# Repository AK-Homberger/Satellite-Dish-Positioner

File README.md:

# Satellite Dish Positioner

This is an automatical satellite dish positioner with an ESP8266 D1 Mini, a compass and an MPU. It controls the satellite dish direction with a Diseqc rotor (azimut) and a linear actuator (elevation). It uses an gyroscope device for elevation and a compass device for azimut control.

The purpose of this device is to support me on the boat with the positioning of the satellite dish from the cabin. But it is also usable for campers and mobile homes.

## Hardware
The rotor is a standard Diseqc dish motor for less than 50 Euro. But for this project we use the motor upside down to move the dish in horizontal ballance. We have to remove the cranked dish connection tube from the motor. But keep the bolt and the nut. We need them to connect the upper and lower 3D-printed joint parts. 

The ESP8266 (in D1 Mini) controls the Diseqc motor with 22 kHz tone signals as defined in the [Diseqc specification](https://www.eutelsat.com/files/PDF/DiSEqC-documentation.zip) (see bus_spec.pdf, section 5 and also positioner_appli_notice.pdf). The ESP8266 generates the signal which has to be modulated on the coax signal line of the motor. I found the necessary circuit and signal generator code on GitHub:(https://github.com/acrerd/Arduino-Diseqc-solar-tracker). Many thanks for the helpful support. That saved me a lot of time. For simplification, I only used the right part of the [circuit](https://github.com/AK-Homberger/Satellite-Dish-Positioner/blob/main/diseqc-interface.pdf) starting with the 100 Ohm resistor. The risistor is directly connected to port D5 on the D1 Mini. This is sufficient to generate a signal that the Diseqc motor is recognising.

The delay values in the Arduino code ( functions write0() and write1() ) had to be adjusted for the faster ESP8266. The delay with 21 microseconds works perfectly to generate a 22 kHz signal.

The motor gets the 12 Volt power via the coax connection. Be careful with the coax connector when the device is powerd. A shortcut between core and shield would instantly destroy the inductor coil (it can only handle about 300 mA).

The motor is able to move from -75 to +75 degrees with an accuracy of 1/16 degree. That is more than sufficient for positioning the azimut.
You just have to position the sat finder in a general south facing direction. Thats all.

The elevation is controlled with a standard small linear actuator which is available for less than 30 Euro. I use here an actuator with 50 mm length. But 25 mm should work also.

In addition to the 22 kHz logic, only four other items are required:

- Step-down-converter 12V to 5V: D24V10F5
- Compass: GY-271 from AzDelivery (install [QMC5883LCompass](https://github.com/mprograms/QMC5883LCompass) library in Arduino)
- 6 axis gyroscope: GY-521 from AzDelivery (install [TinyMPU6050](https://github.com/gabriel-milan/TinyMPU6050) library in Arduino):
- Motor driver:  Adafruit DRV8871 DC Motor Driver

**Be careful with the GY-271 from other sources. Some devices are using a HMC5883L compass instead of a QMC5883L. We need the QMC5883L for this project.**

The compass and the gyroscope are connected to the I2C bus of the D1 Mini (using D1=SCL and D2=SDA). The compass is inside the box on the pcb. The gyroscope is connected with a short 4-wire cable and placed on the back of the satellite dish.

The motor driver is using ports D0 and D6. The 22 kHz signal is generated on port D5.

Schematics and PCB layout is in KiCAD folder.

## Software
The positioner is controlled with a web interface. The ssid and password for WLAN has to be set in the code.

The device is pre-configured for Astra 19.2 and my home location. Please change this for your location and satellite.
You can use one of the free calculators to get the angles for your location and desired setellite (e.g. https://www.satlex.us/en/azel_calc.html). Use "Azimut angle" and "Elevation angle". 

The true north azimut angle needs to be corrected (Az_Offset) to match the magnetic north of the compass (sailors should know how to calculate) and to correct a possible placing error on the pcb. 

The elevation angle must be corrected (El_Offset) with a dish specific value. For my dish this is -18 degrees between dish beam angle and angle of gyroscope mount. The offset has to be calculated only once and defined in the program.

```cpp
//Enter your SSID and PASSWORD
const char* ssid = "ssid";
const char* password = "passwod";

float Astra_Az = 164, Astra_El = 30.19, El_Offset=-18, Az_Offset=-10.0;   // Astra 19.2 position and dish specific offsets
```

With the web interface you can control the positioner. You can do fine tuning for azimut/elevation and switch automatic control between Off, On and R-Off.

R-Off means automatic control for azimut is switched off. Elevation remains on. This is a kind of "night" mode because the Diseqc motor is a bit noisy when constantly re-positioning. The "-Step/Step+" buttons are changing the rotor for 1/8 degree. Which should be sufficient for the desired purpose. It is possible to change it also to 1/16 degree.

Values for Azimut, Elevation, Offsets and Motor Speed can be changed with a "Settings" web page. Changed values are stored in flash memory (EEPROM) of ESP8266. With "Motor Speed" you can define the speed of the linear actuator. The value should be about 700 and defines the Pulse Width Modulation for the actuator. If the dish begins to "swing" you can adjust the value to avoid this.

.

To improve the precision of the compass, it is necessary to calibrate the device before using it. To do the calibration, load and run the [calibration sketch](https://github.com/mprograms/QMC5883LCompass/blob/master/examples/calibration/calibration.ino) from the QMC5883L compass library.

During the calibration process the device have to be moved in all possible directions (see library example). It is probably a good idea to do the calibration before placing the pcb on the dish.

The shown six values have to be set in this line:
```
compass.setCalibration(-1598, 1511, -2365, 872, -1417, 1440);   // Do a calibration for the compass and put your values here!!!
```

For the MPU there is also an calibration function available. See library for [details](https://github.com/gabriel-milan/TinyMPU6050/blob/master/examples/ArduinoIDE_Angles_Example/ArduinoIDE_Angles_Example.ino). But due to the fact that the elevation offset has to be set anyway, it is not necessary to do the calibration for the device, to get the individual offsets.

The following line in the code:
```
experimental::ESP8266WiFiGratuitous::stationKeepAliveSetIntervalMs(5000);
```
is part of the internal [ESP8266WiFi](https://github.com/esp8266/Arduino/blob/master/libraries/ESP8266WiFi/src/ESP8266WiFiGratuitous.h) library. It solves a WLAN connection problem for my router by sending ARP packets every 5 seconds to keep the WLAN connection stable.

If you don't need this, simply comment out the line.

## 3D Prints
The connection between the sat dish and the rotor as well as the other parts are designed with OpenSCAD. The files are stored in the SCAD folder.

You can either use the .scad files with OpenSCAD or you can directly print the .stl files stored [here](https://github.com/AK-Homberger/Satellite-Dish-Positioner/tree/main/SCAD/STL).

The GY-521 gyroscope is placed on the back of the dish in a hoizonal position. The compass is on the pcb facing to south direction. For other directions do a correction in the code with "#define Az_PCB_Correction 90". I had to add 90 degrees to get south direction, 180°.

The connection between the dish and the Diseqc motor has to be very stable. I used 0.2 mm accuracy and 70% fillrate for PLA. Use of ABS is also an option.

## Parts
- Sat dish: [Link](https://www.voelkner.de/products/21807/Telestar-5103309-Camping-SAT-Anlage-ohne-Receiver-Teilnehmer-Anzahl-1.html?ref=43&offer=74abe2d23c3a61dabbbaf20649c0274a&gclid=EAIaIQobChMIhfuapsL67QIVaFXVCh3rzAHpEAYYASABEgIO9vD_BwE)
- Diseqc motor: [Link](https://www.ebay.de/itm/332284938131?chn=ps&norover=1&mkevt=1&mkrid=707-134425-41852-0&mkcid=2&itemid=332284938131&targetid=940585975411&device=c&mktype=pla&googleloc=9043858&poi=&campaignid=10203814992&mkgroupid=101937413437&rlsatarget=pla-940585975411&abcId=1145992&merchantid=112028706&gclid=EAIaIQobChMIg57du6jQ7AIVRtiyCh0ixQoGEAQYAyABEgJfgvD_BwE) or [Link](https://www.wiltanet.de/sat-empfang/diseqc-schalter-motor/diseqc-motor/diseqc-motor/a-120017)
- Linear Actuator (25 or 50 mm): [Link](https://www.ebay.de/itm/750N-25-150-mm-Linear-Actuator-elektrische-Mikro-Linearantrieb-12V-Kraft-IP65/402438285052?_trkparms=aid%3D555021%26algo%3DPL.SIMRVI%26ao%3D1%26asc%3D225078%26meid%3De5d8f347c09a4ba989a35d0217f8cb5c%26pid%3D100008%26rk%3D1%26rkt%3D11%26mehot%3Dpf%26sd%3D383778548269%26itm%3D402438285052%26pmt%3D1%26noa%3D0%26pg%3D2047675%26algv%3DSimplRVIAMLv5WebWithPLRVIOnTopCombiner&_trksid=p2047675.c100008.m2219)
- D1 Mini: AzDelivery (e.g. on Amazon) [Link](https://www.amazon.de/stores/AZDelivery/AZDelivery/page/2DB821D9-4A4B-4FD2-A50B-AE111B57FC93)
- GY-271 compass: AzDelivery (e.g. on Amazon) [Link](https://www.amazon.de/stores/AZDelivery/AZDelivery/page/2DB821D9-4A4B-4FD2-A50B-AE111B57FC93) or [Link](https://www.makershop.de/sensoren/gy-271-hmc5883l/)
- GY-521 gyroscope: AzDelivery (e.g. on Amazon) [Link](https://www.amazon.de/stores/AZDelivery/AZDelivery/page/2DB821D9-4A4B-4FD2-A50B-AE111B57FC93)
- D24V10F5 [Link](https://eckstein-shop.de/Pololu-5V-1A-Step-Down-Spannungsregler-D24V10F5)
- Adafruit DRV8871: [Link](https://eckstein-shop.de/Adafruit-DRV8871-DC-Motor-Driver-Breakout-Board-36A-Max)
- Resistor 51 Ohm [Link](https://www.reichelt.de/de/en/carbon-film-resistor-1-4-w-5-51-ohm-1-4w-51-p1441.html?&nbc=1)
- Resistor 100 Ohm [Link](https://www.reichelt.de/de/en/carbon-film-resistor-1-4-w-5-100-ohms-1-4w-100-p1336.html?&nbc=1)
- Inductor 1 mH - BOU RLB0914-102K [Link](https://www.reichelt.de/index.html?ACTION=446&LA=0&nbc=1&q=bou%20rlb0914-102k)
- Capacitor 56 nF - RND 150MKT563K2E [Link](https://www.reichelt.de/index.html?ACTION=446&LA=0&nbc=1&q=150mkt563k2e%20) or alternative MKP-X2 56N2 [Link](https://www.reichelt.de/de/en/radio-interference-suppression-capacitors-56nf-305v-rm15-mkp-x2-56n2-p173414.html?&nbc=1)
- Capacitor 3,3 µF - TON 3,3/63 [Link](https://www.reichelt.de/index.html?ACTION=446&LA=446&nbc=1&q=ton%203%2C3%2F63)
- Connector 2-pin (*2) [Link](https://www.reichelt.de/de/en/2-pin-terminal-strip-spacing-5-08-akl-101-02-p36605.html?&nbc=1)
- Connector 4-pin [Link](https://www.reichelt.de/de/en/4-pin-terminal-strip-spacing-5-08-akl-101-04-p36607.html?&nbc=1)
- DC Jack [Link](https://www.reichelt.de/de/en/connector-dc-female-bulkhead-delock-89911-p259483.html?&nbc=1)

## Updates
- Version 1.1 - 19.05.2021: Improved 22 kHz signal generation (Issue #5).
- Version 1.0 - 09.02.2021: Added pcb mount correction value. Release version 1.0
- Version 0.6 - 05.02.2021: Added settings page and storage of settings in flash memory.
- Version 0.5 - 07.11.2020: Corrected error in azimut calculation (boundary check 0-360).
- Version 0.4 - 06.11.2020: Changed PCB layout to version 1.1. Larger terminal strips (5.08 mm).
- Version 0.4 - 28.10.2020: Added permanent azimut offset.
- Version 0.3 - 26.10.2020: Separated elevation and elevation offset to work with true elevation angles from calculators. 
- Version 0.2 - 26.10.2020: Initial version.

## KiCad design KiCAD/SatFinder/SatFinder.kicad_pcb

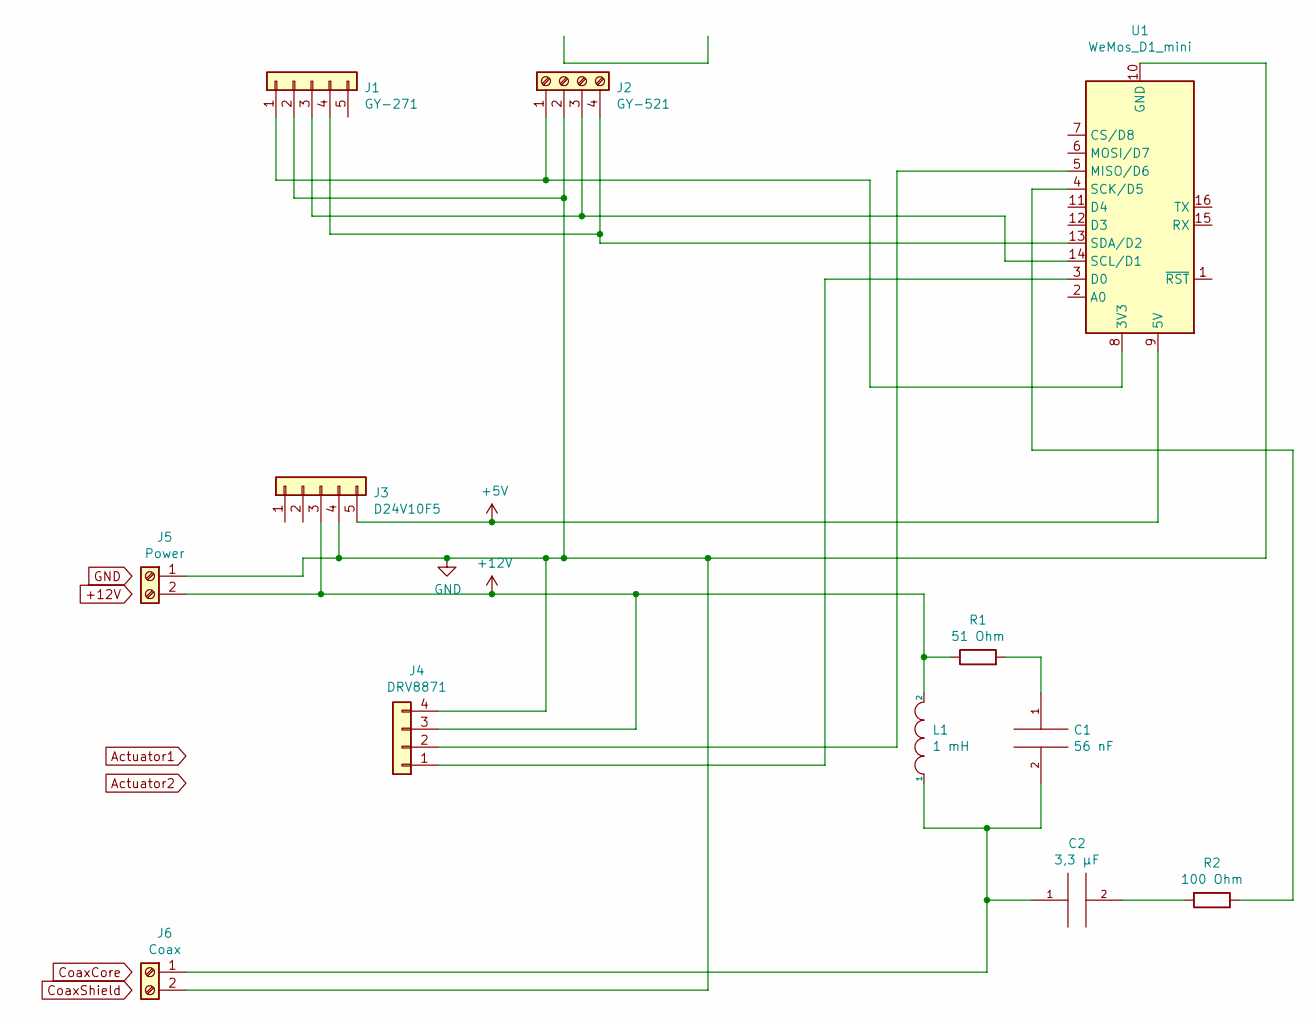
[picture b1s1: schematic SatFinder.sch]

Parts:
C1: 56 nF; C_Rect_L18.0mm_W5.0mm_P15.00mm_FKS3_FKP3
C2: 3,3 µF; CP_Axial_L18.0mm_D8.0mm_P25.00mm_Horizontal
J1: GY-271; PinHeader_1x05_P2.54mm_Vertical
J2: GY-521; TerminalBlock_bornier-4_P5.08mm
J3: D24V10F5; PinHeader_1x05_P2.54mm_Vertical
J4: DRV8871; PinHeader_1x04_P2.54mm_Vertical
J5: Power; TerminalBlock_bornier-2_P5.08mm
J6: Coax; TerminalBlock_bornier-2_P5.08mm
L1: 1 mH; L_Radial_D8.7mm_P5.00mm_Fastron_07HCP
R1: 51 Ohm; R_Axial_DIN0207_L6.3mm_D2.5mm_P7.62mm_Horizontal
R2: 100 Ohm; R_Axial_DIN0207_L6.3mm_D2.5mm_P7.62mm_Horizontal
U1: WeMos_D1_mini; WEMOS_D1_mini_light

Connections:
+5V: J3.5, U1.9 (5V)
+12V: J3.3, J4.3, J5.2, L1.2, R1.1
GND: J1.2, J2.2, J3.4, J4.4, J5.1, J6.2, U1.10 (GND)
unnamed: C1.1, R1.2
unnamed: C1.2, C2.1, J6.1, L1.1
unnamed: C2.2, R2.2
unnamed: J1.1, J2.1, U1.8 (3V3)
unnamed: J1.3, J2.3, U1.14 (SCL/D1)
unnamed: J1.4, J2.4, U1.13 (SDA/D2)
unnamed: J4.1, U1.3 (D0)
unnamed: J4.2, U1.5 (MISO/D6)
unnamed: R2.1, U1.4 (SCK/D5)

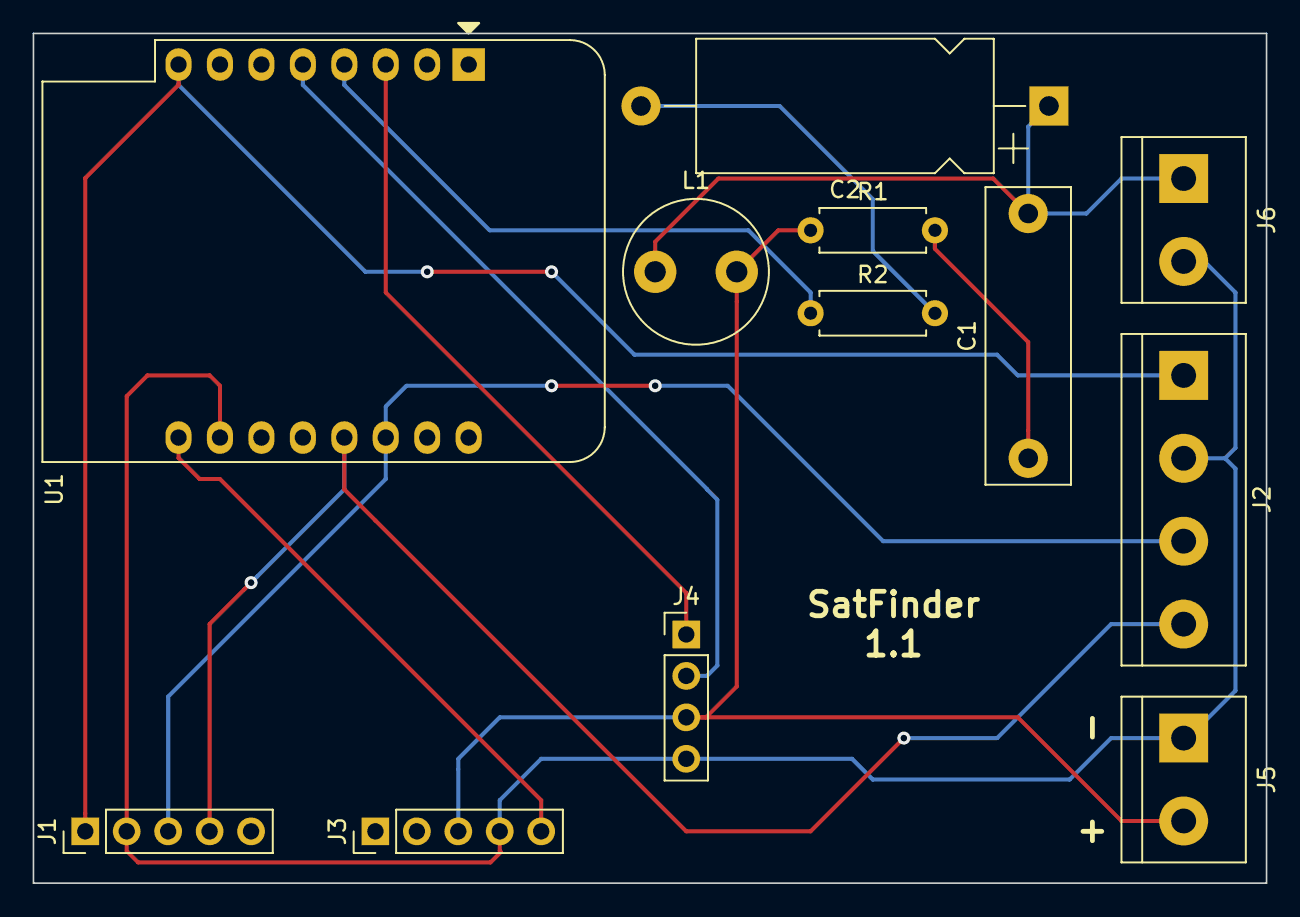
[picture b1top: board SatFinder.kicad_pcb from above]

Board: 2 copper layers, 75.6 x 52.1 mm, 12 parts (0 on the bottom side), 12 nets.

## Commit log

2020-10-26 Added R-Off and corrected compass smoothing.
2020-10-26 Separate elevation and offest to work with standard elevation angles.
2020-10-28 Added permanent azimut offset.
2020-10-29 Added KiCAD files
2020-11-06 Version 1.1
2020-11-07 Corrected error in Azimut calculation (0-360).
2020-11-07 Corrected error in azimut calculation.
2021-02-05 Added settings page
2021-02-09 Version 1.0
2021-04-05 Smaller connector for linear drive.
2021-05-19 V1.1: Improved timing for 22 kHz signal generation.
    Changed delay microseconds from 16/17 to 22 to get 22 kHz signal. The solartracker source code worked on a slower Arduinon. The faster ES82666 needs different delay values.
2021-05-23 V1.1: Improved timing for 22 kHz signal generation.
    Changed delay microseconds from 16/17 to 21 to get 22 kHz signal. The solartracker source code worked on a slower Arduinon. The faster ES82666 needs different delay values.
2021-11-15 Move to src dir and add platformio.ini
2021-11-15 rename to main.cpp
2021-11-15 Functions must be declared prior to use.
2021-11-15 monitor_speed and upload_speed = 115200
2021-11-17 upload_speed = 921600 and OTA lines in platformio.ini
2021-11-17 newline
